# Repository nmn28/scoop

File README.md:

# Scoop - Heart Rate Monitor Project

A heart rate monitoring project using the Seeed Studio XIAO nRF52840 board and MAX30102 sensor. This project provides firmware and visualization tools for real-time heart rate monitoring.

## Project Structure

```
scoop/
├── boards/
│   └── scoop-dev/          # Hardware design files
│       ├── diodelib/       # Component libraries
│       ├── elec/          # PCB design files
│       └── firmware/      # Embedded firmware
│           └── test/      # Example code and tests
├── scoop_sensor_display.py # Python visualization tool
└── README.md
```

## Features

- Real-time heart rate monitoring
- Signal quality detection
- Web-based visualization interface
- Embedded Rust firmware
- Python data processing

## Quick Start

1. Navigate to the firmware directory:
   ```bash
   cd boards/scoop-dev/firmware/test
   ```

2. Follow the [firmware README](boards/scoop-dev/firmware/test/README.md) for detailed setup and usage instructions.

## Documentation

- [Firmware Documentation](boards/scoop-dev/firmware/test/README.md)
- [Hardware Design Files](boards/scoop-dev/)

## License

This project is licensed under the MIT License - see the LICENSE file for details.

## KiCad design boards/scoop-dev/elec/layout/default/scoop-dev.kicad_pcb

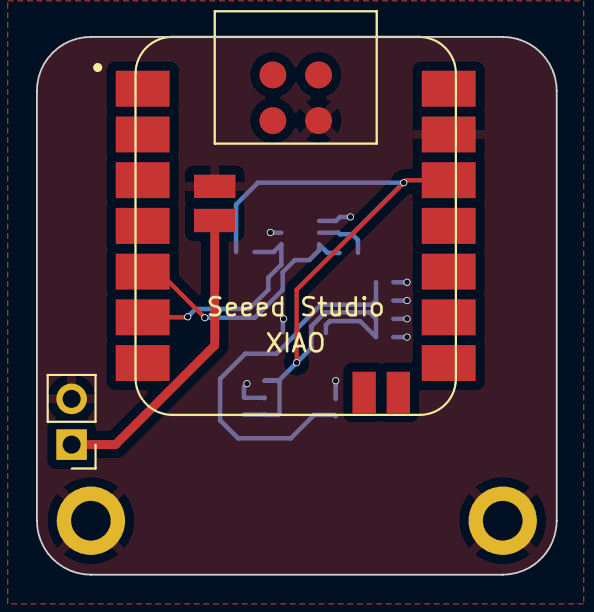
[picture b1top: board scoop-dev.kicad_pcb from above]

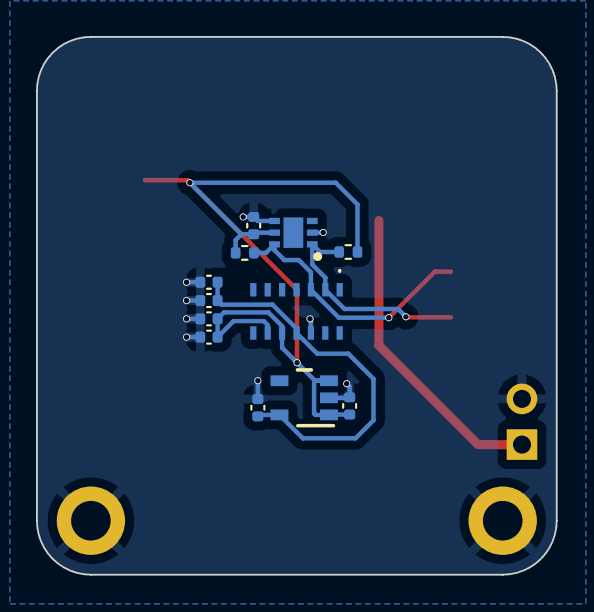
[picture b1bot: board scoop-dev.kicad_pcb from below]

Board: 2 copper layers, 28.9 x 29.9 mm, 16 parts (12 on the bottom side), 6 nets.

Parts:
C1, C3, C5: 16V 100nF X7R ±10% 0402 Multilayer Ceramic Capaci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; C0402
C2: 6.3V 10uF X5R ±20% 0402 Multilayer Ceramic Capaci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; C0402
C4: 10V 4.7uF X5R ±20% 0402 Multilayer Ceramic Capaci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; C0402
C6, C7: 25V 1uF X5R ±10% 0402 Multilayer Ceramic Capacito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; C0402
R1, R2: 62.5mW Thick Film Resistors 50V ±100ppm/℃ ±1% 4.7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; R0402
U1, U2: ?; MountingHole_2.2mm_M2_DIN965_Pad
U3: ?; SON65P200X200X80-7N
U4: ?; MAX30102EFDT
U5: ?; XIAO-nRF52840-Sense-14P-2.54-21X17.8MM
U6: ?; DBV0005A_N
U7: ?; PinHeader_1x02_P2.54mm_Vertical

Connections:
gnd: C1.2, C2.2, C3.2, C4.2, C5.2, C6.2, C7.2, U1.1, U2.1, U3.2, U3.4, U4.12, U5.13, U5.18, U5.21, U6.2, U7.2
scl: R1.1, U3.1, U4.2, U5.6
sda: R2.1, U3.6, U4.3, U5.5
vcc: U5.22, U7.1
vcc-1: C1.1, C4.1, C5.1, C6.1, R1.2, R2.2, U3.5, U4.9, U4.10, U5.12, U6.1, U6.3
vcc-2: C2.1, C3.1, C7.1, U4.11, U6.5

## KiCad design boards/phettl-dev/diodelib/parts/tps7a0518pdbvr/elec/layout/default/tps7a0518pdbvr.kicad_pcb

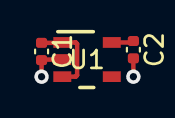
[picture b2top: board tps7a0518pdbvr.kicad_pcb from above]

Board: 2 copper layers, 3 parts (0 on the bottom side), 3 nets.

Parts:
C1, C2: 25V 1uF X5R ±10% 0402 Multilayer Ceramic Capacito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; C0402
U1: ?; DBV0005A_N

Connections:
gnd: C1.2, C2.2, U1.2
ic-vcc: C1.1, U1.1, U1.3
ic-vcc-1: C2.1, U1.5

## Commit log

2024-09-18 [BOARD] add dev board
2024-09-19 [PART] add temp sensor
2024-09-20 [PART] use better temp sensor
2024-09-20 [PART] add xiao
2024-09-23 [BOARD] add pullups
2024-09-23 [BAT] add connectors
2024-09-24 [BOARD] add dimensions
2024-09-30 [VENDOR] components
2024-10-03 [PCB] restore layout
2024-10-03 [FIRMWARE] test
2025-01-16 Initial commit: Heart rate monitoring project with MAX30102 sensor
2025-01-16 docs: Update project documentation with comprehensive setup and usage instructions
